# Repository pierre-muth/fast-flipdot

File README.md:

# fast-flipdot
Driving a flipdot matrix differently. All dots simultaneously. 
story here : https://pierremuth.wordpress.com/2021/02/17/flipping-dots-fast/
video here : https://youtu.be/6l5hH8V9uUo

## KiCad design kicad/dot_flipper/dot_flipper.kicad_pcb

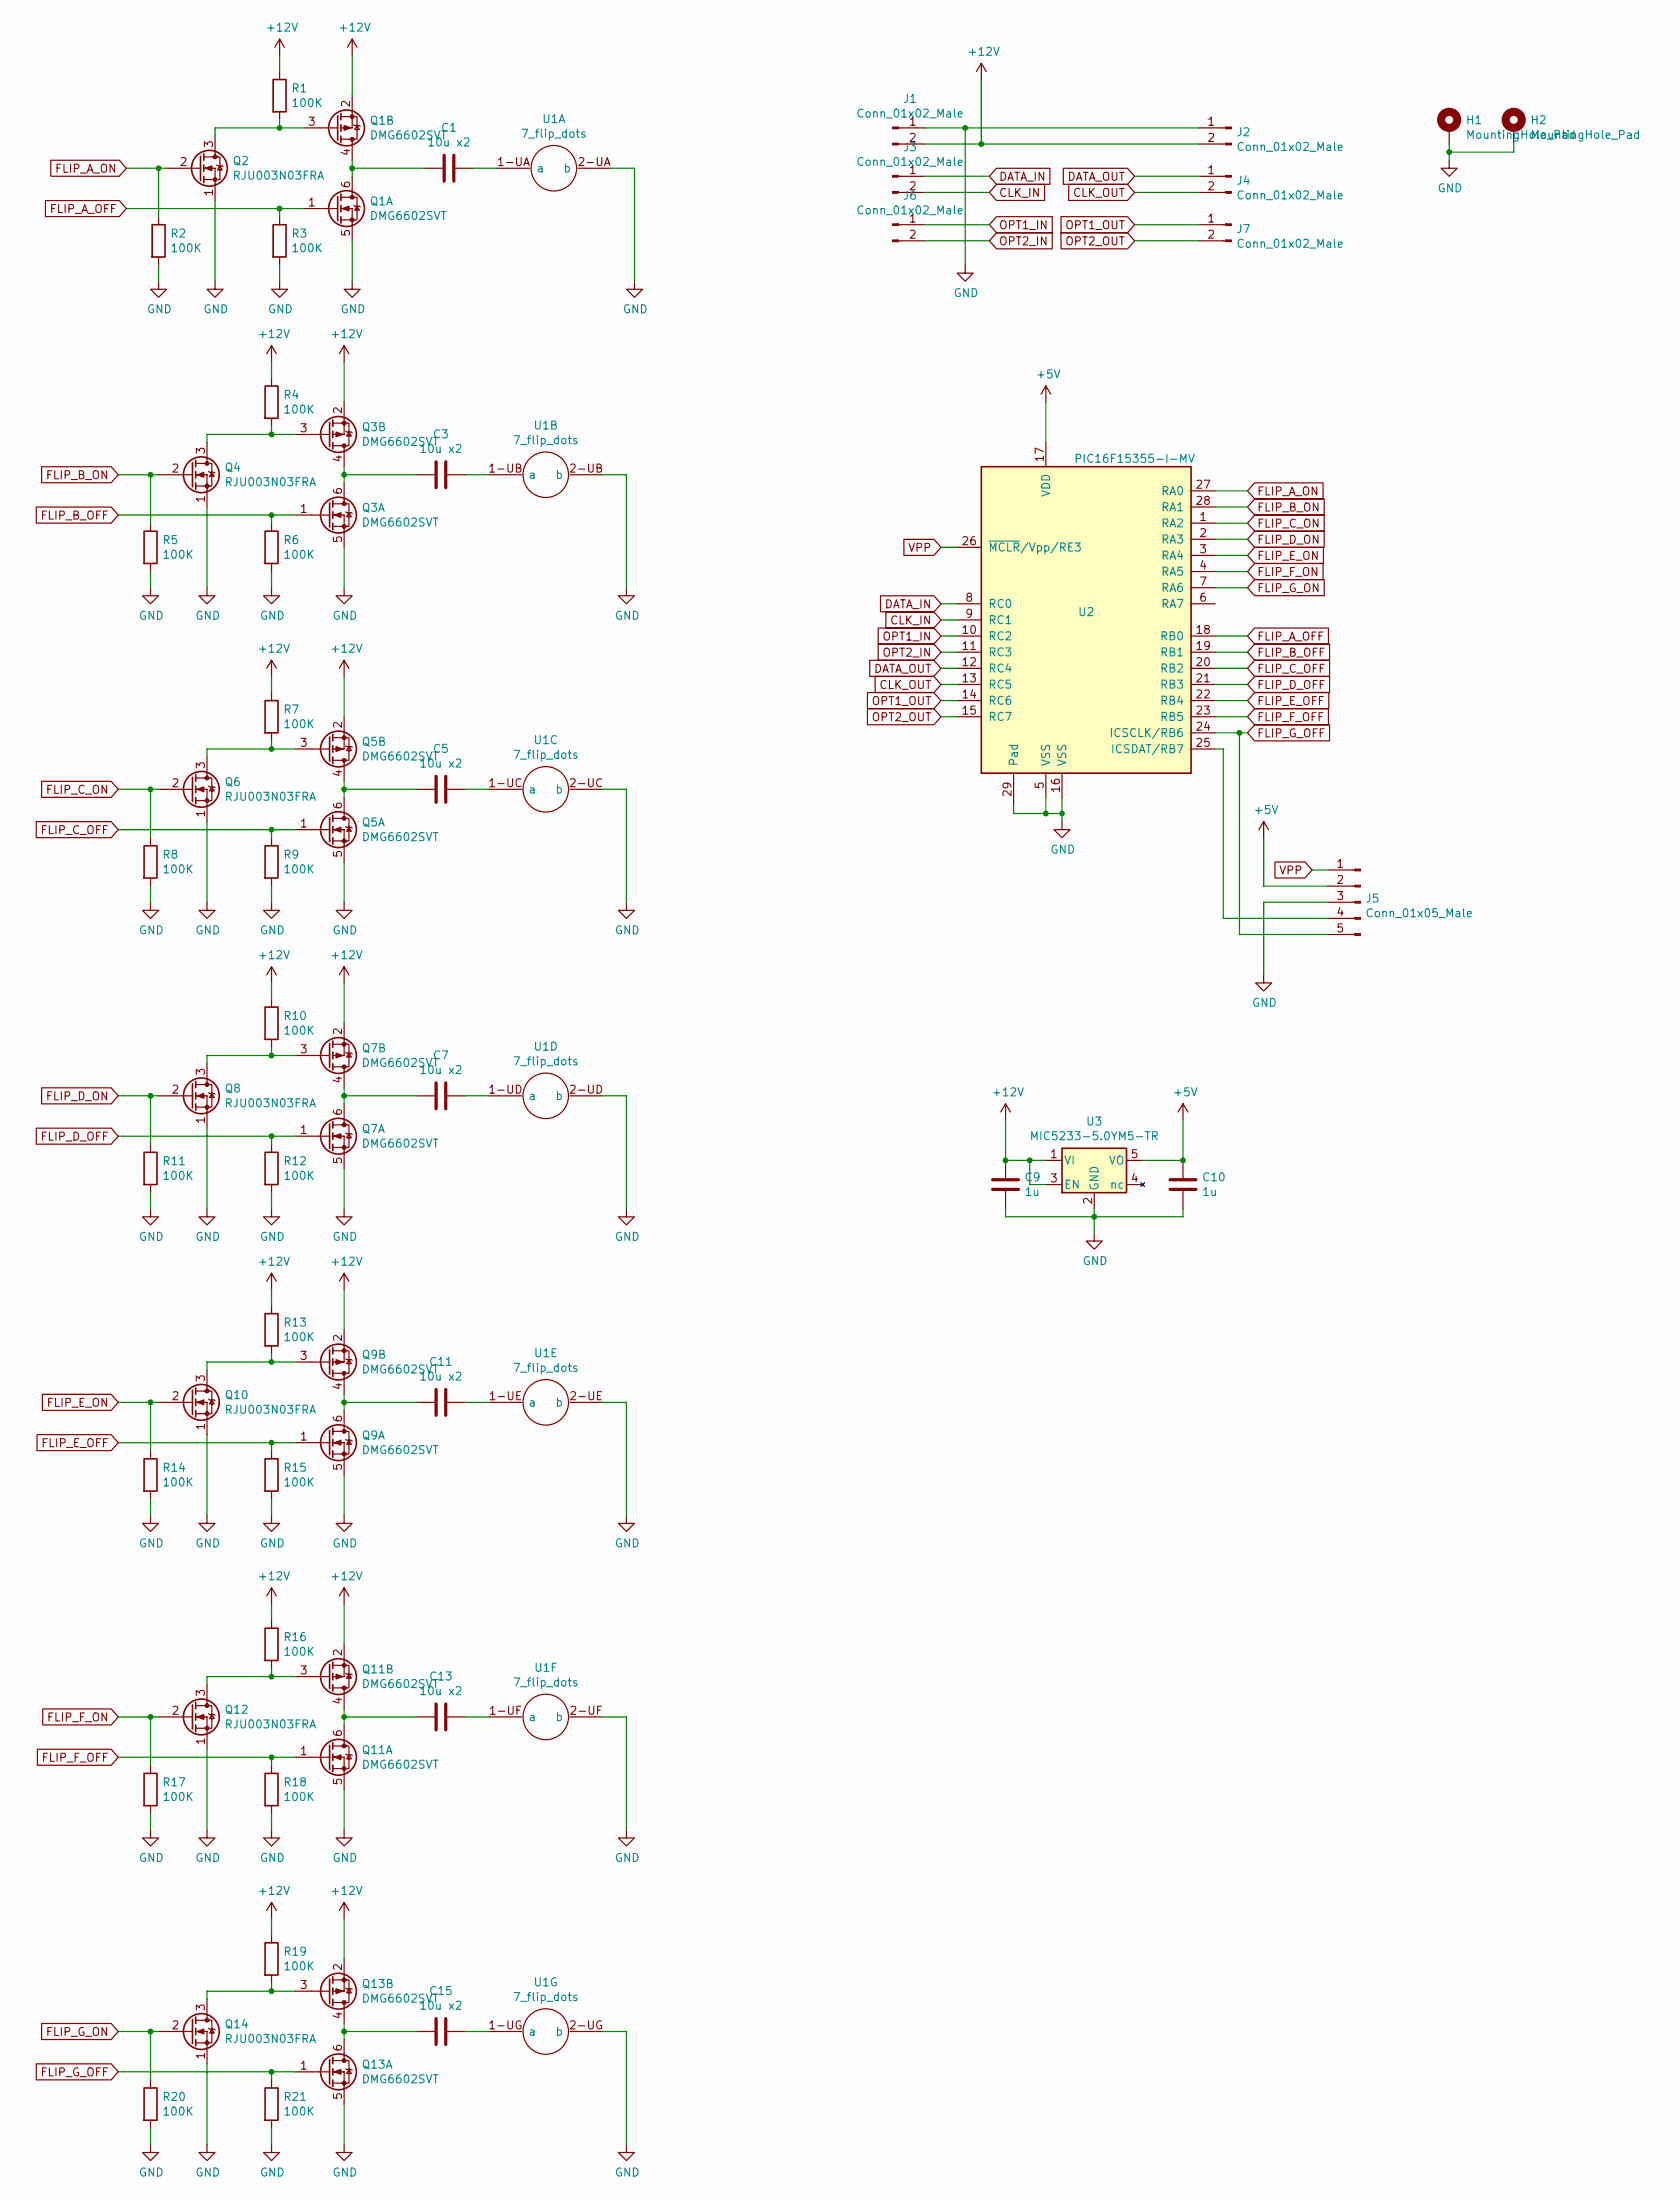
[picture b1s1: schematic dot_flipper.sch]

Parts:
C1, C3, C5, C7, C11, C13, C15: 10u x2; C_1206
C9, C10: 1u; C_0805
H1, H2: MountingHole_Pad; MountingHole_2.2mm_M2_Pad_thin
J1, J2, J3, J4, J6, J7: Conn_01x02_Male; Pin_Header_Straight_1x02_Pitch2.54mm
J5: Conn_01x05_Male; Pin_Header_Straight_1x05_Pitch1.27mm
Q1, Q3, Q5, Q7, Q9, Q11, Q13: DMG6602SVT; SOT-23-6_Handsoldering
Q2, Q4, Q6, Q8, Q10, Q12, Q14: RJU003N03FRA; SOT-23-small
R1, R2, R3, R4, R5, R6, R7, R8, R9, R10, R11, R12, R13, R14, R15, R16, R17, R18, R19, R20, R21: 100K; R_0805
U1: 7_flip_dots
U2: PIC16F15355-I-MV; QFN-28-1EP_4x4mm_Pitch0.4mm_wide
U3: MIC5233-5.0YM5-TR; SOT-23-5_HandSoldering

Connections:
+5V: C10.1, J5.2, U2.17 (VDD), U3.5 (VO)
+12V: C9.1, J1.2, J2.2, Q1.2 (S), Q3.2 (S), Q5.2 (S), Q7.2 (S), Q9.2 (S), Q11.2 (S), Q13.2 (S), R1.1, R4.1, R7.1, R10.1, R13.1, R16.1, R19.1, U3.1 (VI), U3.3 (EN)
CLK_IN: J3.2, U2.9 (RC1)
CLK_OUT: J4.2, U2.13 (RC5)
DATA_IN: J3.1, U2.8 (RC0)
DATA_OUT: J4.1, U2.12 (RC4)
FLIP_A_OFF: Q1.1 (G), R3.1, U2.18 (RB0)
FLIP_A_ON: Q2.2 (G), R2.1, U2.27 (RA0)
FLIP_B_OFF: Q3.1 (G), R6.1, U2.19 (RB1)
FLIP_B_ON: Q4.2 (G), R5.1, U2.28 (RA1)
FLIP_C_OFF: Q5.1 (G), R9.1, U2.20 (RB2)
FLIP_C_ON: Q6.2 (G), R8.1, U2.1 (RA2)
FLIP_D_OFF: Q7.1 (G), R12.1, U2.21 (RB3)
FLIP_D_ON: Q8.2 (G), R11.1, U2.2 (RA3)
FLIP_E_OFF: Q9.1 (G), R15.1, U2.22 (RB4)
FLIP_E_ON: Q10.2 (G), R14.1, U2.3 (RA4)
FLIP_F_OFF: Q11.1 (G), R18.1, U2.23 (RB5)
FLIP_F_ON: Q12.2 (G), R17.1, U2.4 (RA5)
FLIP_G_OFF: J5.5, Q13.1 (G), R21.1, U2.24 (ICSCLK/RB6)
FLIP_G_ON: Q14.2 (G), R20.1, U2.7 (RA6)
GND: C9.2, C10.2, H1.1, H2.1, J1.1, J2.1, J5.3, Q1.5 (S), Q2.1 (S), Q3.5 (S), Q4.1 (S), Q5.5 (S), Q6.1 (S), Q7.5 (S), Q8.1 (S), Q9.5 (S), Q10.1 (S), Q11.5 (S), Q12.1 (S), Q13.5 (S), Q14.1 (S), R2.2, R3.2, R5.2, R6.2, R8.2, R9.2, R11.2, R12.2, R14.2, R15.2, R17.2, R18.2, R20.2, R21.2, U1.2-UA (b), U1.2-UB (b), U1.2-UC (b), U1.2-UD (b), U1.2-UE (b), U1.2-UF (b), U1.2-UG (b), U2.5 (VSS), U2.16 (VSS), U2.29 (Pad), U3.2 (GND)
unnamed: C1.1, U1.1-UA (a)
unnamed: C1.2, Q1.4 (D), Q1.6 (D)
unnamed: C3.1, U1.1-UB (a)
unnamed: C3.2, Q3.4 (D), Q3.6 (D)
unnamed: C5.1, U1.1-UC (a)
unnamed: C5.2, Q5.4 (D), Q5.6 (D)
unnamed: C7.1, U1.1-UD (a)
unnamed: C7.2, Q7.4 (D), Q7.6 (D)
unnamed: C11.1, U1.1-UE (a)
unnamed: C11.2, Q9.4 (D), Q9.6 (D)
unnamed: C13.1, U1.1-UF (a)
unnamed: C13.2, Q11.4 (D), Q11.6 (D)
unnamed: C15.1, U1.1-UG (a)
unnamed: C15.2, Q13.4 (D), Q13.6 (D)
unnamed: J5.4, U2.25 (ICSDAT/RB7)
unnamed: Q1.3 (G), Q2.3 (D), R1.2
unnamed: Q3.3 (G), Q4.3 (D), R4.2
unnamed: Q5.3 (G), Q6.3 (D), R7.2
unnamed: Q7.3 (G), Q8.3 (D), R10.2
unnamed: Q9.3 (G), Q10.3 (D), R13.2
unnamed: Q11.3 (G), Q12.3 (D), R16.2
unnamed: Q13.3 (G), Q14.3 (D), R19.2
OPT1_IN: J6.1, U2.10 (RC2)
OPT1_OUT: J7.1, U2.14 (RC6)
OPT2_IN: J6.2, U2.11 (RC3)
OPT2_OUT: J7.2, U2.15 (RC7)
VPP: J5.1, U2.26 (~MCLR~/Vpp/RE3)

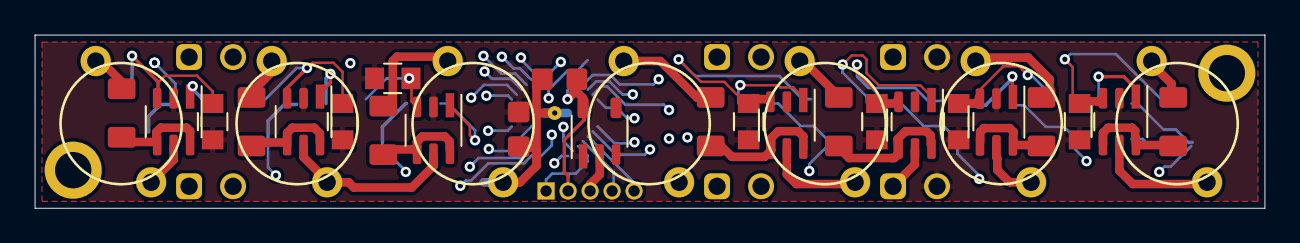
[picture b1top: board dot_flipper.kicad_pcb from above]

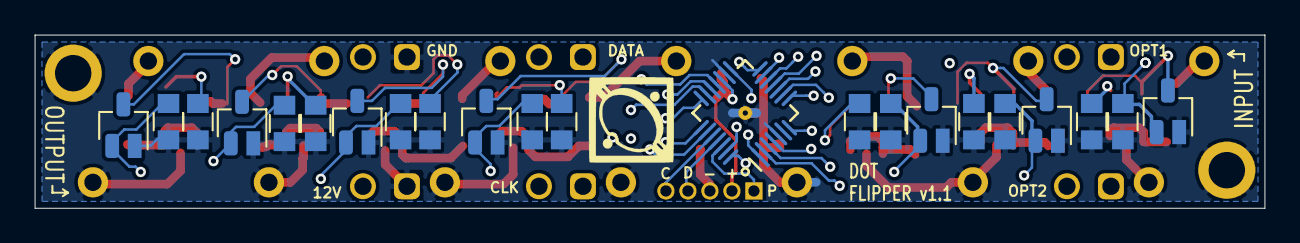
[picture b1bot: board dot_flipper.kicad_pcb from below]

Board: 4 copper layers, 71.0 x 10.0 mm, 56 parts (22 on the bottom side), 48 nets.

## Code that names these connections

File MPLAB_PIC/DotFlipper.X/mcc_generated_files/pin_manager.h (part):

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// get/set IO_RA0 aliases
#define IO_RA0_TRIS                 TRISAbits.TRISA0
#define IO_RA0_LAT                  LATAbits.LATA0
#define IO_RA0_PORT                 PORTAbits.RA0
#define IO_RA0_WPU                  WPUAbits.WPUA0
#define IO_RA0_OD                   ODCONAbits.ODCA0
#define IO_RA0_ANS                  ANSELAbits.ANSA0
#define IO_RA0_SetHigh()            do { LATAbits.LATA0 = 1; } while(0)
#define IO_RA0_SetLow()             do { LATAbits.LATA0 = 0; } while(0)
#define IO_RA0_Toggle()             do { LATAbits.LATA0 = ~LATAbits.LATA0; } while(0)
#define IO_RA0_GetValue()           PORTAbits.RA0
#define IO_RA0_SetDigitalInput()    do { TRISAbits.TRISA0 = 1; } while(0)
#define IO_RA0_SetDigitalOutput()   do { TRISAbits.TRISA0 = 0; } while(0)
#define IO_RA0_SetPullup()          do { WPUAbits.WPUA0 = 1; } while(0)
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// get/set IO_RA1 aliases
#define IO_RA1_TRIS                 TRISAbits.TRISA1
#define IO_RA1_LAT                  LATAbits.LATA1
#define IO_RA1_PORT                 PORTAbits.RA1
#define IO_RA1_WPU                  WPUAbits.WPUA1
#define IO_RA1_OD                   ODCONAbits.ODCA1
#define IO_RA1_ANS                  ANSELAbits.ANSA1
#define IO_RA1_SetHigh()            do { LATAbits.LATA1 = 1; } while(0)
#define IO_RA1_SetLow()             do { LATAbits.LATA1 = 0; } while(0)
#define IO_RA1_Toggle()             do { LATAbits.LATA1 = ~LATAbits.LATA1; } while(0)
#define IO_RA1_GetValue()           PORTAbits.RA1
#define IO_RA1_SetDigitalInput()    do { TRISAbits.TRISA1 = 1; } while(0)
#define IO_RA1_SetDigitalOutput()   do { TRISAbits.TRISA1 = 0; } while(0)
#define IO_RA1_SetPullup()          do { WPUAbits.WPUA1 = 1; } while(0)
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// get/set IO_RA2 aliases
#define IO_RA2_TRIS                 TRISAbits.TRISA2
#define IO_RA2_LAT                  LATAbits.LATA2
#define IO_RA2_PORT                 PORTAbits.RA2
#define IO_RA2_WPU                  WPUAbits.WPUA2
#define IO_RA2_OD                   ODCONAbits.ODCA2
#define IO_RA2_ANS                  ANSELAbits.ANSA2
#define IO_RA2_SetHigh()            do { LATAbits.LATA2 = 1; } while(0)
#define IO_RA2_SetLow()             do { LATAbits.LATA2 = 0; } while(0)
#define IO_RA2_Toggle()             do { LATAbits.LATA2 = ~LATAbits.LATA2; } while(0)
#define IO_RA2_GetValue()           PORTAbits.RA2
#define IO_RA2_SetDigitalInput()    do { TRISAbits.TRISA2 = 1; } while(0)
#define IO_RA2_SetDigitalOutput()   do { TRISAbits.TRISA2 = 0; } while(0)
#define IO_RA2_SetPullup()          do { WPUAbits.WPUA2 = 1; } while(0)
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// get/set IO_RA3 aliases
#define IO_RA3_TRIS                 TRISAbits.TRISA3
#define IO_RA3_LAT                  LATAbits.LATA3
#define IO_RA3_PORT                 PORTAbits.RA3
#define IO_RA3_WPU                  WPUAbits.WPUA3
#define IO_RA3_OD                   ODCONAbits.ODCA3
#define IO_RA3_ANS                  ANSELAbits.ANSA3
#define IO_RA3_SetHigh()            do { LATAbits.LATA3 = 1; } while(0)
#define IO_RA3_SetLow()             do { LATAbits.LATA3 = 0; } while(0)
#define IO_RA3_Toggle()             do { LATAbits.LATA3 = ~LATAbits.LATA3; } while(0)
#define IO_RA3_GetValue()           PORTAbits.RA3
#define IO_RA3_SetDigitalInput()    do { TRISAbits.TRISA3 = 1; } while(0)
#define IO_RA3_SetDigitalOutput()   do { TRISAbits.TRISA3 = 0; } while(0)
#define IO_RA3_SetPullup()          do { WPUAbits.WPUA3 = 1; } while(0)
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// get/set IO_RA4 aliases
#define IO_RA4_TRIS                 TRISAbits.TRISA4
#define IO_RA4_LAT                  LATAbits.LATA4
#define IO_RA4_PORT                 PORTAbits.RA4
#define IO_RA4_WPU                  WPUAbits.WPUA4
#define IO_RA4_OD                   ODCONAbits.ODCA4
#define IO_RA4_ANS                  ANSELAbits.ANSA4
#define IO_RA4_SetHigh()            do { LATAbits.LATA4 = 1; } while(0)
#define IO_RA4_SetLow()             do { LATAbits.LATA4 = 0; } while(0)
#define IO_RA4_Toggle()             do { LATAbits.LATA4 = ~LATAbits.LATA4; } while(0)
#define IO_RA4_GetValue()           PORTAbits.RA4
#define IO_RA4_SetDigitalInput()    do { TRISAbits.TRISA4 = 1; } while(0)
#define IO_RA4_SetDigitalOutput()   do { TRISAbits.TRISA4 = 0; } while(0)
#define IO_RA4_SetPullup()          do { WPUAbits.WPUA4 = 1; } while(0)
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// get/set IO_RA5 aliases
#define IO_RA5_TRIS                 TRISAbits.TRISA5
#define IO_RA5_LAT                  LATAbits.LATA5
#define IO_RA5_PORT                 PORTAbits.RA5
#define IO_RA5_WPU                  WPUAbits.WPUA5
#define IO_RA5_OD                   ODCONAbits.ODCA5
#define IO_RA5_ANS                  ANSELAbits.ANSA5
#define IO_RA5_SetHigh()            do { LATAbits.LATA5 = 1; } while(0)
#define IO_RA5_SetLow()             do { LATAbits.LATA5 = 0; } while(0)
#define IO_RA5_Toggle()             do { LATAbits.LATA5 = ~LATAbits.LATA5; } while(0)
#define IO_RA5_GetValue()           PORTAbits.RA5
#define IO_RA5_SetDigitalInput()    do { TRISAbits.TRISA5 = 1; } while(0)
#define IO_RA5_SetDigitalOutput()   do { TRISAbits.TRISA5 = 0; } while(0)
#define IO_RA5_SetPullup()          do { WPUAbits.WPUA5 = 1; } while(0)
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// get/set IO_RA6 aliases
#define IO_RA6_TRIS                 TRISAbits.TRISA6
#define IO_RA6_LAT                  LATAbits.LATA6
#define IO_RA6_PORT                 PORTAbits.RA6
#define IO_RA6_WPU                  WPUAbits.WPUA6
#define IO_RA6_OD                   ODCONAbits.ODCA6
#define IO_RA6_ANS                  ANSELAbits.ANSA6
#define IO_RA6_SetHigh()            do { LATAbits.LATA6 = 1; } while(0)
#define IO_RA6_SetLow()             do { LATAbits.LATA6 = 0; } while(0)
#define IO_RA6_Toggle()             do { LATAbits.LATA6 = ~LATAbits.LATA6; } while(0)
#define IO_RA6_GetValue()           PORTAbits.RA6
#define IO_RA6_SetDigitalInput()    do { TRISAbits.TRISA6 = 1; } while(0)
#define IO_RA6_SetDigitalOutput()   do { TRISAbits.TRISA6 = 0; } while(0)
#define IO_RA6_SetPullup()          do { WPUAbits.WPUA6 = 1; } while(0)
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// get/set IO_RB0 aliases
#define IO_RB0_TRIS                 TRISBbits.TRISB0
#define IO_RB0_LAT                  LATBbits.LATB0
#define IO_RB0_PORT                 PORTBbits.RB0
#define IO_RB0_WPU                  WPUBbits.WPUB0
#define IO_RB0_OD                   ODCONBbits.ODCB0
#define IO_RB0_ANS                  ANSELBbits.ANSB0
#define IO_RB0_SetHigh()            do { LATBbits.LATB0 = 1; } while(0)
#define IO_RB0_SetLow()             do { LATBbits.LATB0 = 0; } while(0)
#define IO_RB0_Toggle()             do { LATBbits.LATB0 = ~LATBbits.LATB0; } while(0)
#define IO_RB0_GetValue()           PORTBbits.RB0
#define IO_RB0_SetDigitalInput()    do { TRISBbits.TRISB0 = 1; } while(0)
#define IO_RB0_SetDigitalOutput()   do { TRISBbits.TRISB0 = 0; } while(0)
#define IO_RB0_SetPullup()          do { WPUBbits.WPUB0 = 1; } while(0)
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// get/set IO_RB1 aliases
#define IO_RB1_TRIS                 TRISBbits.TRISB1
#define IO_RB1_LAT                  LATBbits.LATB1
#define IO_RB1_PORT                 PORTBbits.RB1
#define IO_RB1_WPU                  WPUBbits.WPUB1
#define IO_RB1_OD                   ODCONBbits.ODCB1
#define IO_RB1_ANS                  ANSELBbits.ANSB1
#define IO_RB1_SetHigh()            do { LATBbits.LATB1 = 1; } while(0)
#define IO_RB1_SetLow()             do { LATBbits.LATB1 = 0; } while(0)
#define IO_RB1_Toggle()             do { LATBbits.LATB1 = ~LATBbits.LATB1; } while(0)
#define IO_RB1_GetValue()           PORTBbits.RB1
#define IO_RB1_SetDigitalInput()    do { TRISBbits.TRISB1 = 1; } while(0)
#define IO_RB1_SetDigitalOutput()   do { TRISBbits.TRISB1 = 0; } while(0)
#define IO_RB1_SetPullup()          do { WPUBbits.WPUB1 = 1; } while(0)
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// get/set IO_RB2 aliases
#define IO_RB2_TRIS                 TRISBbits.TRISB2
#define IO_RB2_LAT                  LATBbits.LATB2
#define IO_RB2_PORT                 PORTBbits.RB2
#define IO_RB2_WPU                  WPUBbits.WPUB2
#define IO_RB2_OD                   ODCONBbits.ODCB2
#define IO_RB2_ANS                  ANSELBbits.ANSB2
#define IO_RB2_SetHigh()            do { LATBbits.LATB2 = 1; } while(0)
#define IO_RB2_SetLow()             do { LATBbits.LATB2 = 0; } while(0)
#define IO_RB2_Toggle()             do { LATBbits.LATB2 = ~LATBbits.LATB2; } while(0)
#define IO_RB2_GetValue()           PORTBbits.RB2
#define IO_RB2_SetDigitalInput()    do { TRISBbits.TRISB2 = 1; } while(0)
#define IO_RB2_SetDigitalOutput()   do { TRISBbits.TRISB2 = 0; } while(0)
#define IO_RB2_SetPullup()          do { WPUBbits.WPUB2 = 1; } while(0)
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// get/set IO_RB3 aliases
#define IO_RB3_TRIS                 TRISBbits.TRISB3
#define IO_RB3_LAT                  LATBbits.LATB3
#define IO_RB3_PORT                 PORTBbits.RB3
#define IO_RB3_WPU                  WPUBbits.WPUB3
#define IO_RB3_OD                   ODCONBbits.ODCB3
#define IO_RB3_ANS                  ANSELBbits.ANSB3
#define IO_RB3_SetHigh()            do { LATBbits.LATB3 = 1; } while(0)
#define IO_RB3_SetLow()             do { LATBbits.LATB3 = 0; } while(0)
#define IO_RB3_Toggle()             do { LATBbits.LATB3 = ~LATBbits.LATB3; } while(0)
#define IO_RB3_GetValue()           PORTBbits.RB3
#define IO_RB3_SetDigitalInput()    do { TRISBbits.TRISB3 = 1; } while(0)
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
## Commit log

2021-02-18 upload kicad files
2021-02-18 upload ESP32 code
2021-02-18 upload Java code
2021-02-18 upload image
2021-02-18 upload PIC code

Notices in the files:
MPLAB_PIC/DotFlipper.X/mcc_generated_files/pin_manager.h:
(c) 2018 Microchip Technology Inc. and its subsidiaries.
